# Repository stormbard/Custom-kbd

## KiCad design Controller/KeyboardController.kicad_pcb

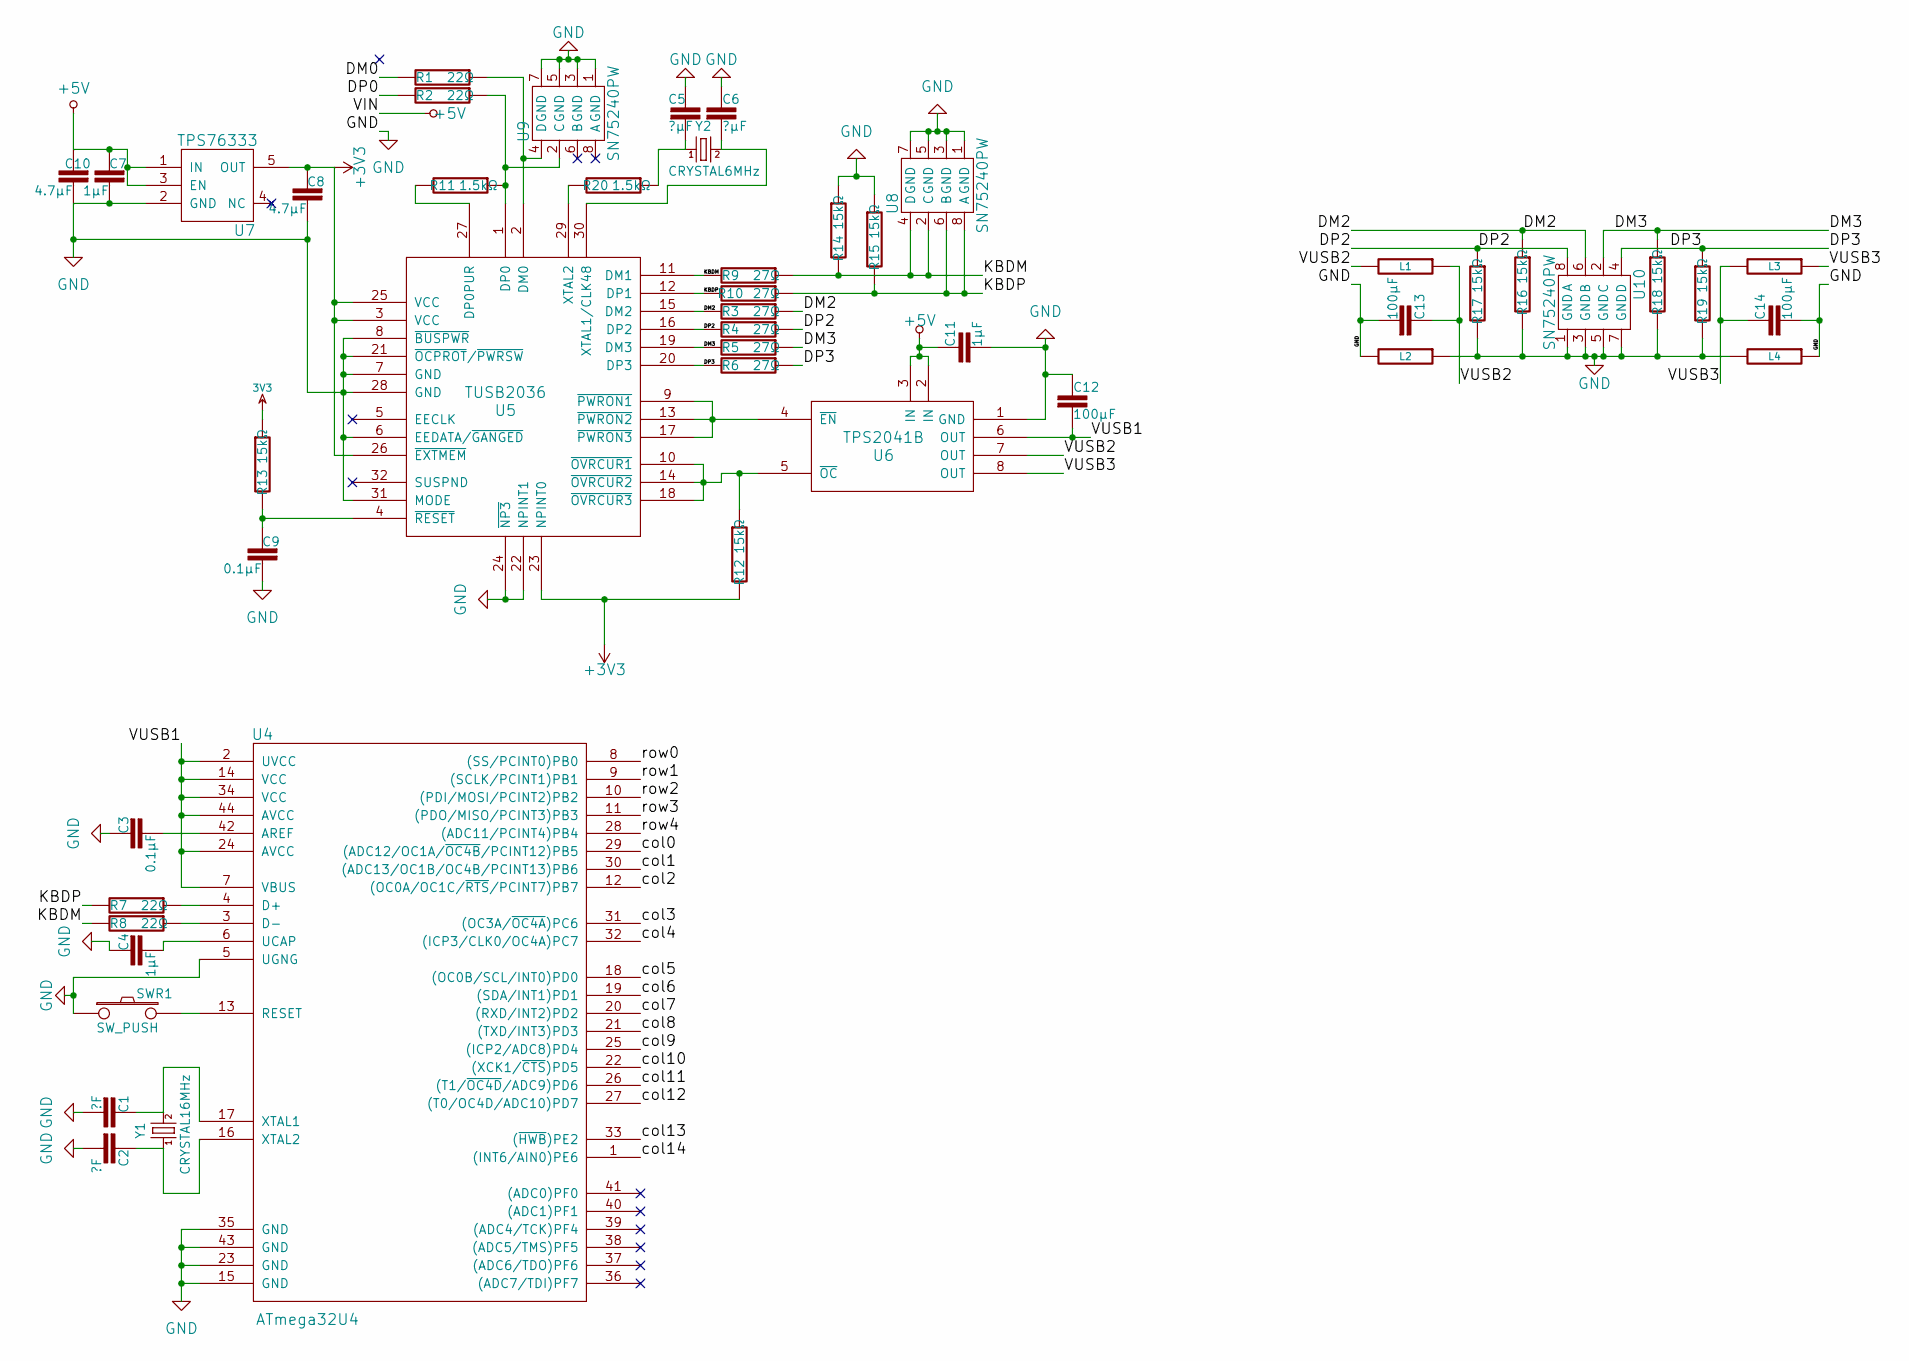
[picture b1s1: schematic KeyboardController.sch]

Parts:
C1, C2: ?F
C3, C9: 0.1µF
C4, C7, C11: 1µF
C5, C6: ?µF
C8, C10: 4.7µF
C12, C13, C14: 100µF
L1, L2, L3: R
L4: L
R1, R2, R7, R8: 22Ω
R3, R4, R5, R6, R9, R10: 27Ω
R11, R20: 1.5kΩ
R12, R13, R14, R15, R16, R17, R18, R19: 15kΩ
SWR1: SW_PUSH
U4: ATmega32U4
U5: TUSB2036
U6: TPS2041B
U7: TPS76333
U8, U9, U10: SN75240PW
Y1: CRYSTAL16MHz
Y2: CRYSTAL6MHz

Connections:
3V3: R13.1
+3V3: C8.2, R12.2, U5.3 (VCC), U5.23 (NPINT0), U5.25 (VCC), U5.26 (~EXTMEM), U7.5 (OUT)
+5V: C7.2, C10.2, C11.1, U6.2 (IN), U6.3 (IN), U7.1 (IN), U7.3 (EN)
/DM2: R3.1, R3.2, R16.1, U5.15 (DM2), U10.6 (B)
/DM3: R5.1, R5.2, R18.1, U5.19 (DM3), U10.2 (C)
/DP2: R4.1, R4.2, R17.1, U5.16 (DP2), U10.8 (A)
/DP3: R6.1, R6.2, R19.1, U5.20 (DP3), U10.4 (D)
/KBDM: R8.2, R9.1, R9.2, R14.2, U5.11 (DM1), U8.2 (C), U8.4 (D)
/KBDP: R7.2, R10.1, R10.2, R15.2, U5.12 (DP1), U8.6 (B), U8.8 (A)
/VUSB1: C12.2, U4.2 (UVCC), U4.7 (VBUS), U4.14 (VCC), U4.24 (AVCC), U4.34 (VCC), U4.44 (AVCC), U6.6 (OUT)
/col0: U4.29 ((ADC12/OC1A/~OC4B~/PCINT12)PB5)
/col1: U4.30 ((ADC13/OC1B/OC4B/PCINT13)PB6)
/col2: U4.12 ((OC0A/OC1C/~RTS~/PCINT7)PB7)
/col3: U4.31 ((OC3A/~OC4A~)PC6)
/col4: U4.32 ((ICP3/CLK0/OC4A)PC7)
/col5: U4.18 ((OC0B/SCL/INT0)PD0)
/col6: U4.19 ((SDA/INT1)PD1)
/col7: U4.20 ((RXD/INT2)PD2)
/col8: U4.21 ((TXD/INT3)PD3)
/col9: U4.25 ((ICP2/ADC8)PD4)
/col10: U4.22 ((XCK1/~CTS~)PD5)
/col11: U4.26 ((T1/~OC4D~/ADC9)PD6)
/col12: U4.27 ((T0/OC4D/ADC10)PD7)
/col13: U4.33 ((~HWB~)PE2)
/col14: U4.1 ((INT6/AIN0)PE6)
/row0: U4.8 ((SS/PCINT0)PB0)
/row1: U4.9 ((SCLK/PCINT1)PB1)
/row2: U4.10 ((PDI/MOSI/PCINT2)PB2)
/row3: U4.11 ((PDO/MISO/PCINT3)PB3)
/row4: U4.28 ((ADC11/PCINT4)PB4)
GND: C1.2, C2.2, C3.2, C4.2, C5.1, C6.1, C7.1, C8.1, C9.1, C10.1, C11.2, C12.1, C13.2, C14.2, L2.1, L2.2, L4.1, L4.2, R14.1, R15.1, R16.2, R17.2, R18.2, R19.2, SWR1.1, U4.5 (UGNG), U4.15 (GND), U4.23 (GND), U4.35 (GND), U4.43 (GND), U5.6 (EEDATA/~GANGED), U5.7 (GND), U5.8 (~BUSPWR), U5.21 (~OCPROT~/~PWRSW), U5.22 (NPINT1), U5.24 (~NP3), U5.28 (GND), U5.31 (MODE), U6.1 (GND), U7.2 (GND), U8.1 (GND), U8.3 (GND), U8.5 (GND), U8.7 (GND), U9.1 (GND), U9.3 (GND), U9.5 (GND), U9.7 (GND), U10.1 (GND), U10.3 (GND), U10.5 (GND), U10.7 (GND)
unnamed: C1.1, U4.17 (XTAL1), Y1.2
unnamed: C2.1, U4.16 (XTAL2), Y1.1
unnamed: C3.1, U4.42 (AREF)
unnamed: C4.1, U4.6 (UCAP)
unnamed: C5.2, R20.1, Y2.1
unnamed: C6.2, U5.30 (XTAL1/CLK48), Y2.2
unnamed: C9.2, R13.2, U5.4 (~RESET)
unnamed: R1.1, U5.2 (DM0), U9.4 (D)
unnamed: R7.1, U4.4 (D+)
unnamed: R8.1, U4.3 (D-)
unnamed: R2.1, R11.1, U5.1 (DP0), U9.2 (C)
unnamed: R11.2, U5.27 (DP0PUR)
unnamed: R12.1, U5.10 (~OVRCUR1), U5.14 (~OVRCUR2), U5.18 (~OVRCUR3), U6.5 (~OC)
unnamed: R20.2, U5.29 (XTAL2)
unnamed: SWR1.2, U4.13 (RESET)
unnamed: U5.9 (~PWRON1), U5.13 (~PWRON2), U5.17 (~PWRON3), U6.4 (~EN)

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
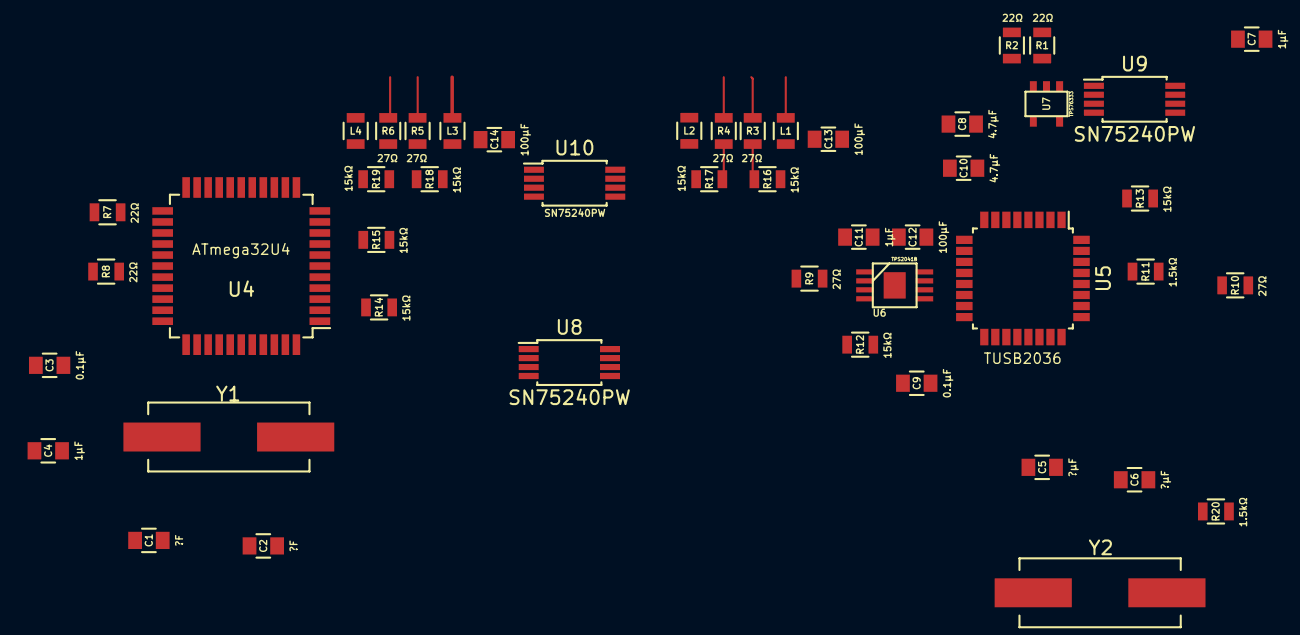
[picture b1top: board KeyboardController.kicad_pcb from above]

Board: 2 copper layers, 47 parts (0 on the bottom side), 27 nets.

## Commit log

2014-12-18 :space_invader: Added .gitattributes
2014-12-18 Initial files for custom keyboard
2015-01-05 Changes to Schematic and PCB. Addition of a plate file.
2015-01-05 Adding in netlist
2015-01-06 Adding in libraries for other components
2015-04-14 latest changes to pcb and plate
    latest changes to pcb and plate
